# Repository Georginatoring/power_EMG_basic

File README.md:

# power_EMG_basic
Main PCB board for EMG signals

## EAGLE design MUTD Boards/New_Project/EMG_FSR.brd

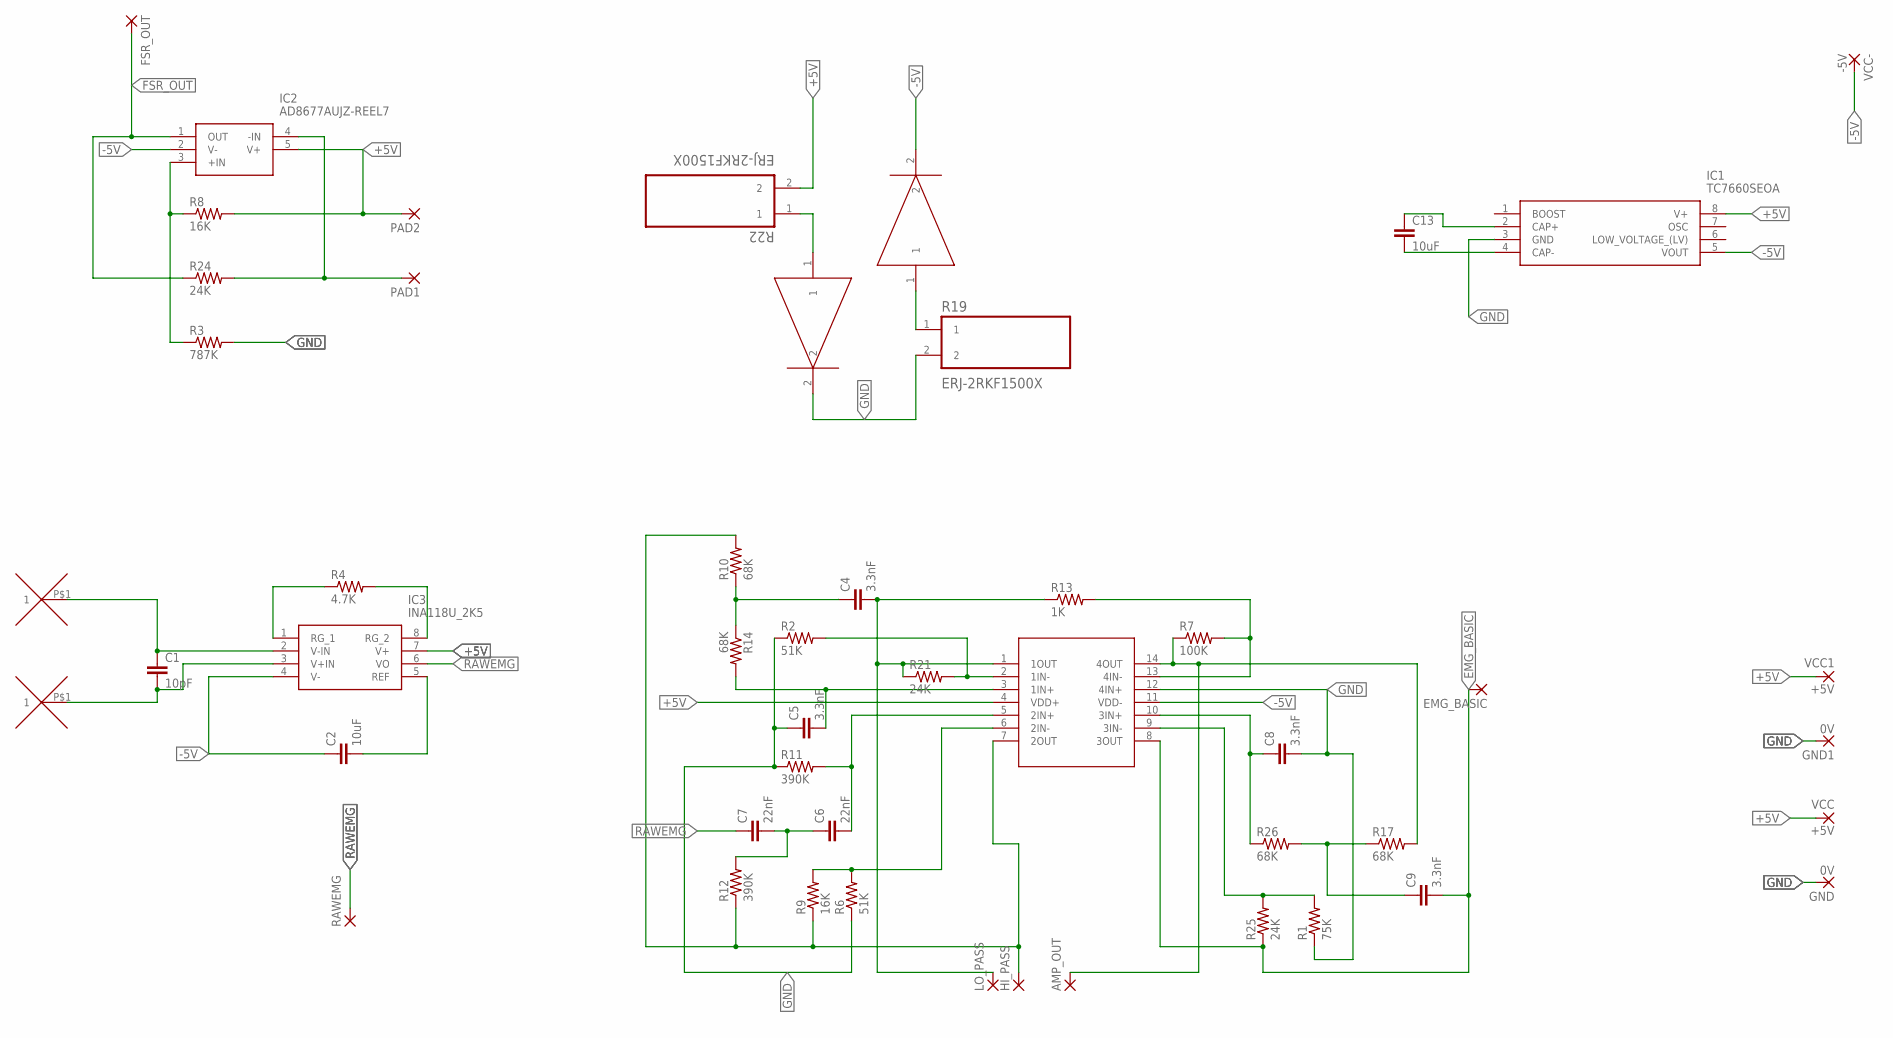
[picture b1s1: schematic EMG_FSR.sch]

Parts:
AMP_OUT: 1,6/0,8
BLUE: RESC0402X40N
C1: 10pF; HPC0201
C2: 10uF; C0805
C4, C5, C8, C9: 3.3nF; C1206
C6, C7: 22nF; C0805
C13: 10uF; C0805K
EMG_BASIC: 1,6/0,8
FSR_OUT: 1,6/0,8
GND, GND1: 0V; 1,6/0,8
HI_PASS: 1,6/0,8
IC1: TC7660SEOA; SOIC127P600X175-8N
IC2: AD8677AUJZ-REEL7; SOT95P280X100-5N
IC3: INA118U_2K5; SOIC127P600X175-8N
LO_PASS: 1,6/0,8
PAD1, PAD2: SMD2; SMD1,27-2,54
R1: 75K; R0402
R2, R6: 51K; R0402
R3: 787K; R0805
R4: 4.7K; R0402
R7: 100K; R1005
R8, R9: 16K; R0402
R10, R14, R17, R26: 68K; R0402
R11, R12: 390K; R0603
R13: 1K; R0402
R19, R22: ERJ-2RKF1500X; RESC1005X40N
R21, R24, R25: 24K; R0402
RAWEMG: 1,6/0,8
RED: RESC0402X40N
U$1: TLC2274-HT; SOP65P640X120-14N
U$2, U$3: EMG_VIA
VCC, VCC1: +5V; 1,6/0,8
VCC-: -5V; 1,6/0,8

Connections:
+5V: IC1.8 (V+), IC2.5 (V+), IC3.7 (V+), PAD2.1, R8.2, R22.2, U$1.4 (VDD+), VCC.1, VCC1.1
-5V: BLUE.2, C2.1, IC1.5 (VOUT), IC2.2 (V-), IC3.4 (V-), U$1.11 (VDD-), VCC-.1
EMG_BASIC: C9.2, EMG_BASIC.1, R25.1, U$1.8 (3OUT)
FSR_OUT: FSR_OUT.1, IC2.1 (OUT), R24.1
GND: C5.1, C8.2, GND.1, GND1.1, IC1.3 (GND), R1.1, R2.1, R3.2, R6.1, R11.1, R19.2, RED.2, U$1.12 (4IN+)
unnamed: C13.1, IC1.2 (CAP+)
unnamed: C13.2, IC1.4 (CAP-)
unnamed: C1.1, IC3.2 (V-IN), U$2.P$1
unnamed: R22.1, RED.1
unnamed: C1.2, IC3.3 (V+IN), U$3.P$1
unnamed: BLUE.1, R19.1
unnamed: IC2.4 (-IN), PAD1.1, R24.2
unnamed: IC2.3 (+IN), R3.1, R8.1
unnamed: C2.2, IC3.5 (REF)
unnamed: IC3.1 (RG_1), R4.1
unnamed: IC3.8 (RG_2), R4.2
unnamed: C4.2, LO_PASS.1, R13.1, R21.1, U$1.1 (1OUT)
unnamed: AMP_OUT.1, R7.1, R17.2, U$1.14 (4OUT)
unnamed: R7.2, R13.2, U$1.13 (4IN-)
unnamed: R2.2, R21.2, U$1.2 (1IN-)
unnamed: C5.2, R14.2, U$1.3 (1IN+)
unnamed: C4.1, R10.1, R14.1
unnamed: C6.1, C7.2, R12.2
unnamed: C6.2, R11.2, U$1.5 (2IN+)
unnamed: R6.2, R9.2, U$1.6 (2IN-)
unnamed: C9.1, R17.1, R26.2
unnamed: C8.1, R26.1, U$1.10 (3IN+)
unnamed: R1.2, R25.2, U$1.9 (3IN-)
PIN7: HI_PASS.1, R9.1, R10.2, R12.1, U$1.7 (2OUT)
RAWEMG: C7.1, IC3.6 (VO), RAWEMG.1

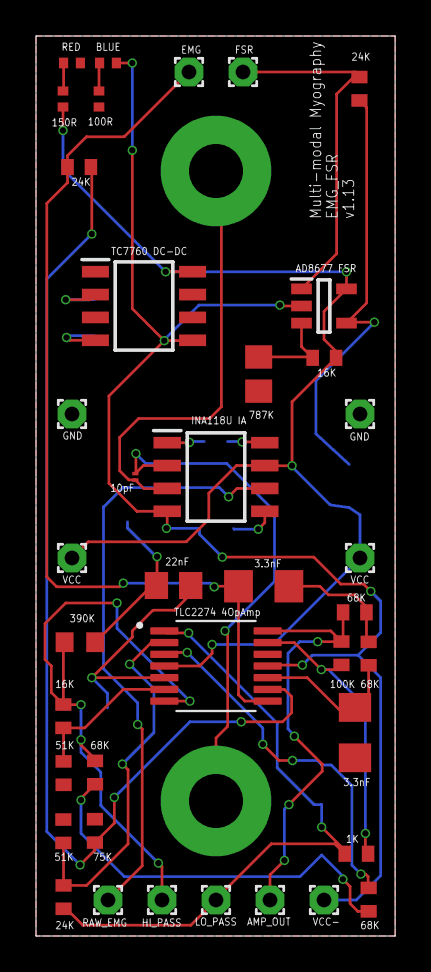
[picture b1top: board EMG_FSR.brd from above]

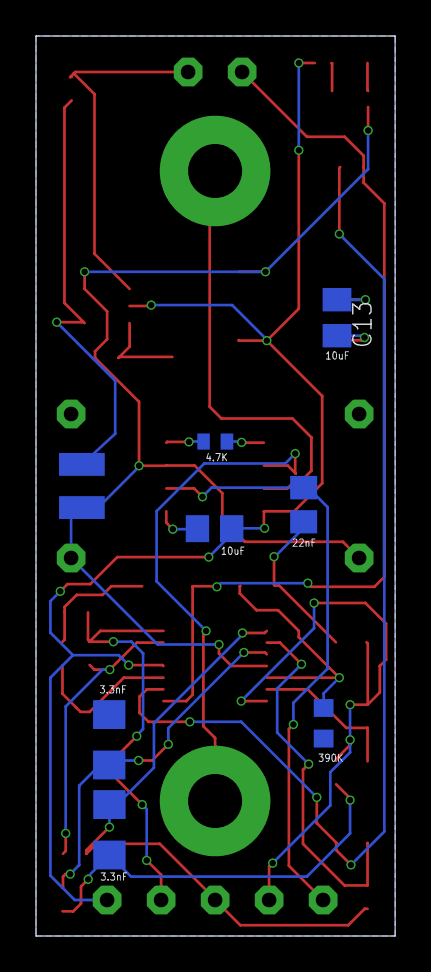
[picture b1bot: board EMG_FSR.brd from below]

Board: 2 copper layers, 19.9 x 50.0 mm, 50 parts (9 on the bottom side), 30 nets.

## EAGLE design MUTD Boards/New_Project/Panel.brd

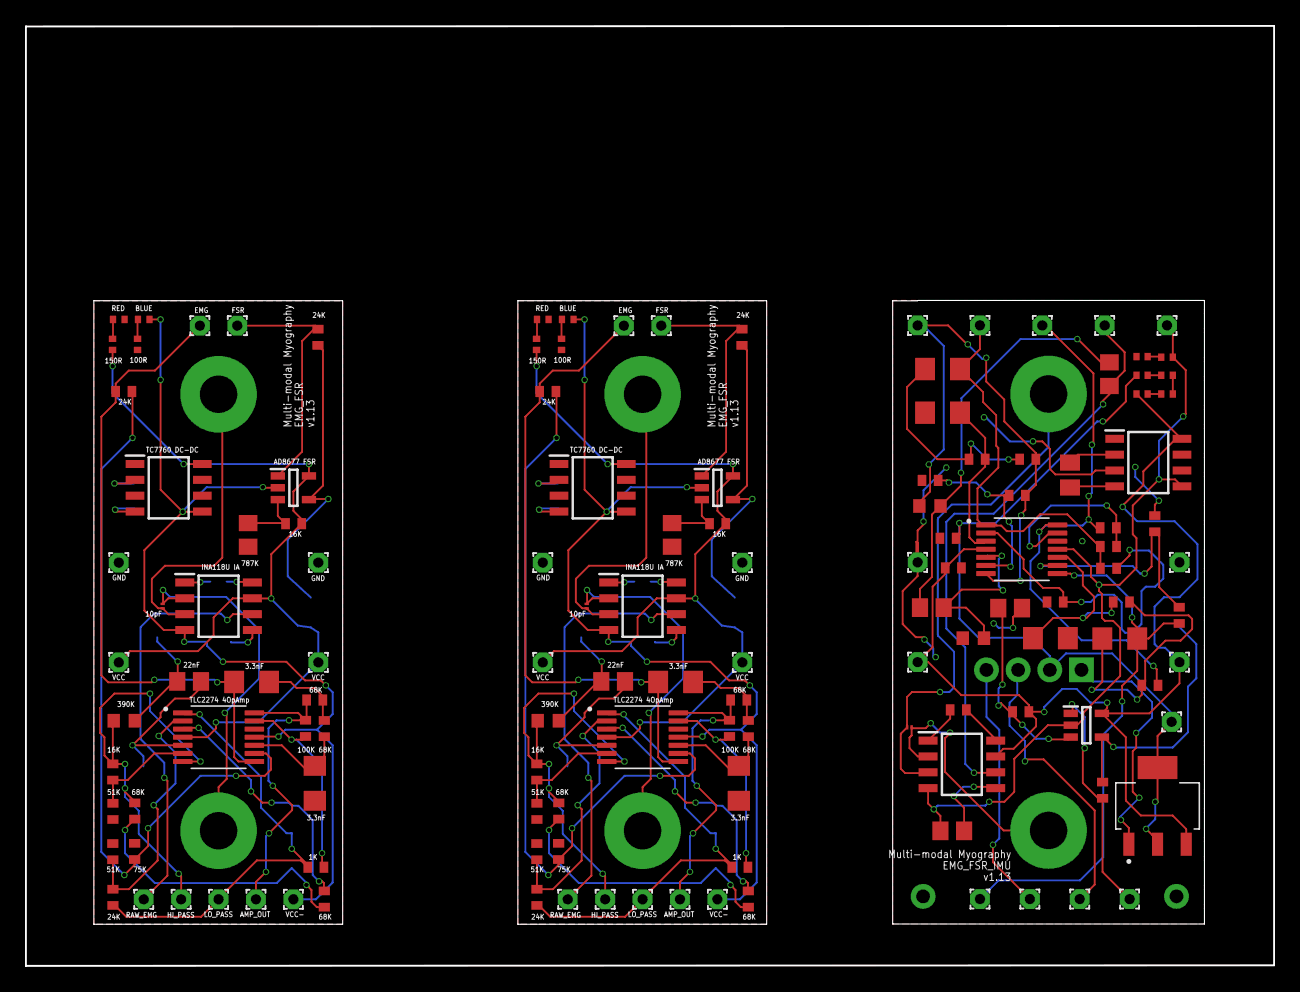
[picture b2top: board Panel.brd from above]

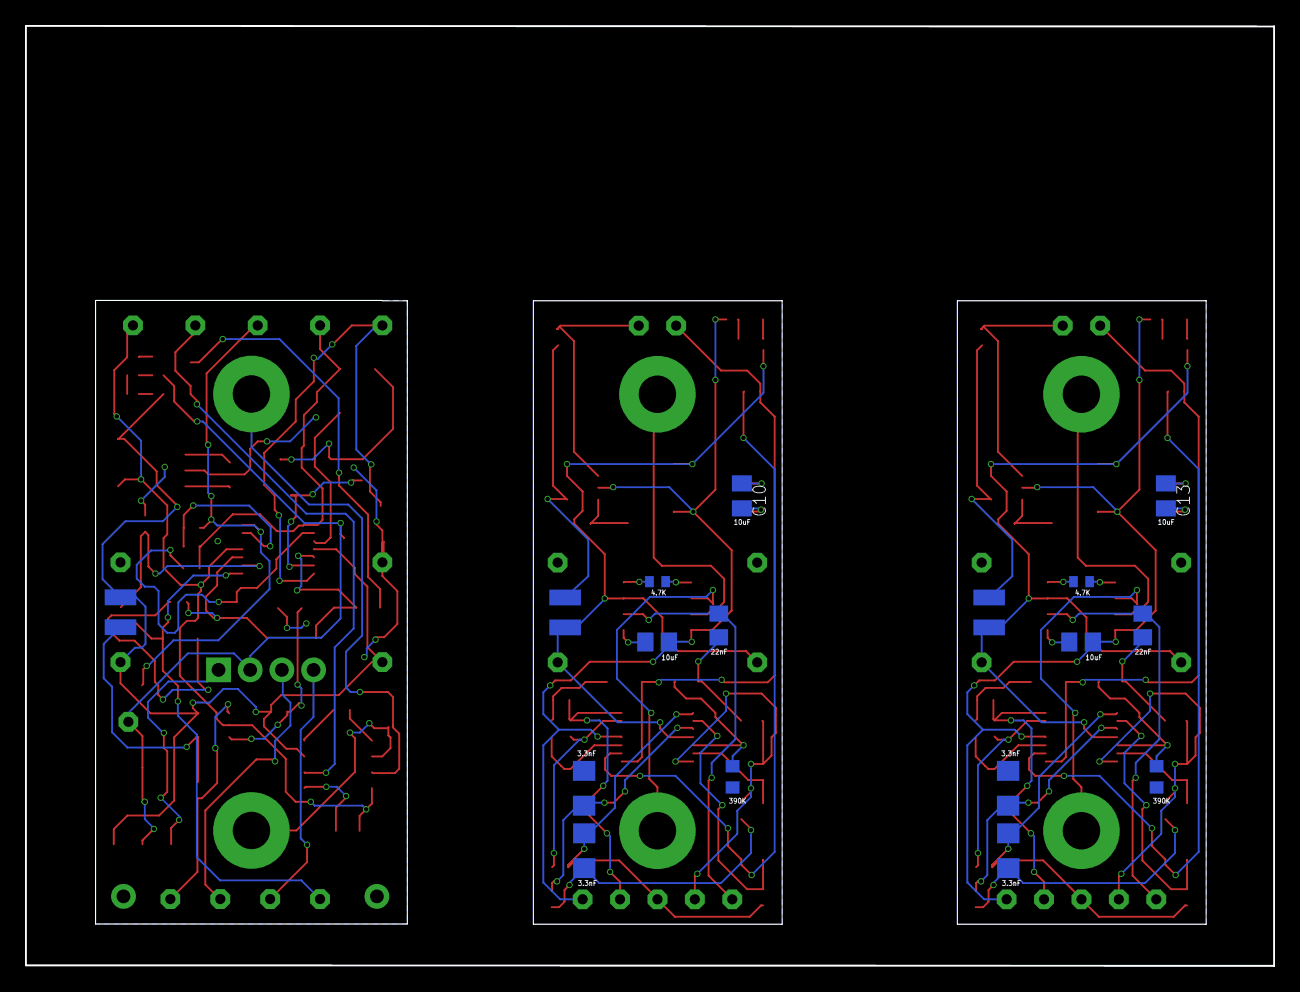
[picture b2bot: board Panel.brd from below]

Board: 2 copper layers, 100.1 x 75.4 mm, 159 parts (20 on the bottom side), 94 nets.

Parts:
+3.3V1: 1,6/0,8
AMP_OUT, AMP_OUT1, AMP_OUT4: 1,6/0,8
BLUE, BLUE1, BLUE4: RESC0402X40N
C1, C3, C39: 10pF; HPC0201
C2, C11, C43: 10uF; C0805
C4, C5, C8, C9, C12, C14, C17, C18, C44, C45, C48, C49: 3.3nF; C1206
C6, C7, C15, C16, C46, C47: 22nF; C0805
C10, C13, C42: 10uF; C0805K
C40, C41: 1uF; C0402
EMG_BASIC, EMG_BASIC1: 1,6/0,8
EMG_OUT1: 1,6/0,8
FSR_OUT, FSR_OUT1, FSR_OUT4: 1,6/0,8
GND, GND1, GND2, GND3, GND8, GND9: 0V; 1,6/0,8
HI_PASS, HI_PASS1, HI_PASS4: 1,6/0,8
IC1, IC4, IC13: TC7660SEOA; SOIC127P600X175-8N
IC2, IC5, IC14: AD8677AUJZ-REEL7; SOT95P280X100-5N
IC3, IC6, IC15: INA118U_2K5; SOIC127P600X175-8N
IMU1: IMU
LO_PASS, LO_PASS1, LO_PASS4: 1,6/0,8
ORANGE1: RESC0402X40N
PAD1, PAD2, PAD3, PAD4, PAD9, PAD10: SMD1,27-2,54
R1, R5, R82: 75K; R0402
R2, R6, R29, R37, R90, R99: 51K; R0402
R3, R35, R97: 787K; R0805
R4, R36, R98: 4.7K; R0402
R7, R38, R100: 100K; R1005
R8, R9, R39, R40, R101, R102: 16K; R0402
R10, R14, R15, R17, R23, R26, R27, R34, R83, R87, R88, R96: 68K; R0402
R11, R12, R16, R18, R84, R85: 390K; R0603
R13, R20, R86: 1K; R0402
R19, R22, R28, R31, R89, R92, R93: ERJ-2RKF1500X; RESC1005X40N
R21, R24, R25, R30, R32, R33, R91, R94, R95: 24K; R0402
RAWEMG, RAWEMG1, RAWEMG4: 1,6/0,8
RED, RED1, RED4: RESC0402X40N
SCL1: 1,6/0,8
SDA1: 1,6/0,8
U2: AZ1117EH-3.3TRG1; SOT230P700X180-4N
U$1, U$4, U$13: TLC2274-HT; SOP65P640X120-14N
U$2, U$3, U$5, U$6, U$14, U$15: EMG_VIA
VCC, VCC1, VCC2, VCC3, VCC8, VCC9: +5V; 1,6/0,8
VCC-, VCC-1, VCC-4: -5V; 1,6/0,8

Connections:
+3.3V1: +3.3V1.1, C40.1, IMU1.+3.3V, R93.2, U2.2, U2.4
+5V: IC1.8, IC2.5, IC3.7, PAD2.1, R8.2, R22.2, U$1.4, VCC.1, VCC1.1
+5V1: IC4.8, IC5.5, IC6.7, PAD4.1, R31.2, R39.2, U$4.4, VCC2.1, VCC3.1
+5V4: C41.1, IC13.8, IC14.5, IC15.7, PAD10.1, R92.2, R101.2, U2.3, U$13.4, VCC8.1, VCC9.1
-5V: BLUE.2, C2.1, IC1.5, IC2.2, IC3.4, U$1.11, VCC-.1
-5V1: BLUE1.2, C11.1, IC4.5, IC5.2, IC6.4, U$4.11, VCC-1.1
-5V4: BLUE4.2, C43.1, IC13.5, IC14.2, IC15.4, U$13.11, VCC-4.1
EMG_BASIC: C9.2, EMG_BASIC.1, R25.1, U$1.8
EMG_BASIC1: C18.2, EMG_BASIC1.1, R33.1, U$4.8
EMG_BASIC4: C49.2, EMG_OUT1.1, R95.1, U$13.8
FSR_OUT: FSR_OUT.1, IC2.1, R24.1
FSR_OUT1: FSR_OUT1.1, IC5.1, R32.1
FSR_OUT4: FSR_OUT4.1, IC14.1, R94.1
GND: C5.1, C8.2, GND.1, GND1.1, IC1.3, R1.1, R2.1, R3.2, R6.1, R11.1, R19.2, RED.2, U$1.12
GND1: C14.1, C17.2, GND2.1, GND3.1, IC4.3, R5.1, R16.1, R28.2, R29.1, R35.2, R37.1, RED1.2, U$4.12
GND4: C40.2, C41.2, C45.1, C48.2, GND8.1, GND9.1, IC13.3, IMU1.GND, ORANGE1.2, R82.1, R84.1, R89.2, R90.1, R97.2, R99.1, RED4.2, U2.1, U$13.12
unnamed: C13.1, IC1.2
unnamed: C13.2, IC1.4
unnamed: C1.1, IC3.2, U$2.P$1
unnamed: R22.1, RED.1
unnamed: C1.2, IC3.3, U$3.P$1
unnamed: BLUE.1, R19.1
unnamed: IC2.4, PAD1.1, R24.2
unnamed: C10.1, IC4.2
unnamed: C10.2, IC4.4
unnamed: IC2.3, R3.1, R8.1
unnamed: C2.2, IC3.5
unnamed: IC3.1, R4.1
unnamed: IC3.8, R4.2
unnamed: C4.2, LO_PASS.1, R13.1, R21.1, U$1.1
unnamed: IC5.4, PAD3.1, R32.2
unnamed: IC5.3, R35.1, R39.1
unnamed: AMP_OUT.1, R7.1, R17.2, U$1.14
unnamed: R7.2, R13.2, U$1.13
unnamed: R2.2, R21.2, U$1.2
unnamed: C5.2, R14.2, U$1.3
unnamed: C4.1, R10.1, R14.1
unnamed: C3.1, IC6.2, U$5.P$1
unnamed: C6.1, C7.2, R12.2
unnamed: C6.2, R11.2, U$1.5
unnamed: C11.2, IC6.5
unnamed: R6.2, R9.2, U$1.6
unnamed: C9.1, R17.1, R26.2
unnamed: C8.1, R26.1, U$1.10
unnamed: IC6.1, R36.1
unnamed: R1.2, R25.2, U$1.9
unnamed: IC6.8, R36.2
unnamed: C12.2, LO_PASS1.1, R20.1, R30.1, U$4.1
unnamed: AMP_OUT1.1, R27.2, R38.1, U$4.14
unnamed: R20.2, R38.2, U$4.13
unnamed: R29.2, R30.2, U$4.2
unnamed: C14.2, R23.2, U$4.3
unnamed: C12.1, R15.1, R23.1
unnamed: C15.2, R16.2, U$4.5
unnamed: C15.1, C16.2, R18.2
unnamed: R37.2, R40.2, U$4.6
unnamed: C18.1, R27.1, R34.2
unnamed: C17.1, R34.1, U$4.10
unnamed: R5.2, R33.2, U$4.9
unnamed: R31.1, RED1.1
unnamed: BLUE1.1, R28.1
unnamed: C3.2, IC6.3, U$6.P$1
unnamed: C42.1, IC13.2
unnamed: C42.2, IC13.4
unnamed: IC14.4, PAD9.1, R94.2
unnamed: IC14.3, R97.1, R101.1
unnamed: C39.1, IC15.2, U$14.P$1
unnamed: C43.2, IC15.5
unnamed: IC15.1, R98.1
unnamed: IC15.8, R98.2
unnamed: C44.2, LO_PASS4.1, R86.1, R91.1, U$13.1
unnamed: AMP_OUT4.1, R88.2, R100.1, U$13.14
unnamed: R86.2, R100.2, U$13.13
unnamed: R90.2, R91.2, U$13.2
unnamed: C45.2, R87.2, U$13.3
unnamed: C44.1, R83.1, R87.1
unnamed: C46.2, R84.2, U$13.5
unnamed: C46.1, C47.2, R85.2
unnamed: R99.2, R102.2, U$13.6
unnamed: C49.1, R88.1, R96.2
unnamed: C48.1, R96.1, U$13.10
unnamed: R82.2, R95.2, U$13.9
unnamed: R92.1, RED4.1
unnamed: BLUE4.1, R89.1
unnamed: C39.2, IC15.3, U$15.P$1
unnamed: IMU1.SDA, SDA1.1
unnamed: IMU1.SCL, SCL1.1
unnamed: ORANGE1.1, R93.1
PIN1: HI_PASS1.1, R15.2, R18.1, R40.1, U$4.7
PIN4: HI_PASS4.1, R83.2, R85.1, R102.1, U$13.7
PIN7: HI_PASS.1, R9.1, R10.2, R12.1, U$1.7
RAWEMG: C7.1, IC3.6, RAWEMG.1
RAWEMG1: C16.1, IC6.6, RAWEMG1.1
RAWEMG4: C47.1, IC15.6, RAWEMG4.1

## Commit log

2020-10-05 Add files via upload
    V1.1 & libraries
2020-10-05 Set EMG Electrode Locations
2020-10-05 Located Some Parts
2020-10-09 Add files via upload
    finished IMU layout including silkscreen
2021-03-11 Add files via upload
    version 2 EMG & FSR
